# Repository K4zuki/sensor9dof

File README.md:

# sensor9dof
BMI160/BMM150 sensor board for MurataBLE board

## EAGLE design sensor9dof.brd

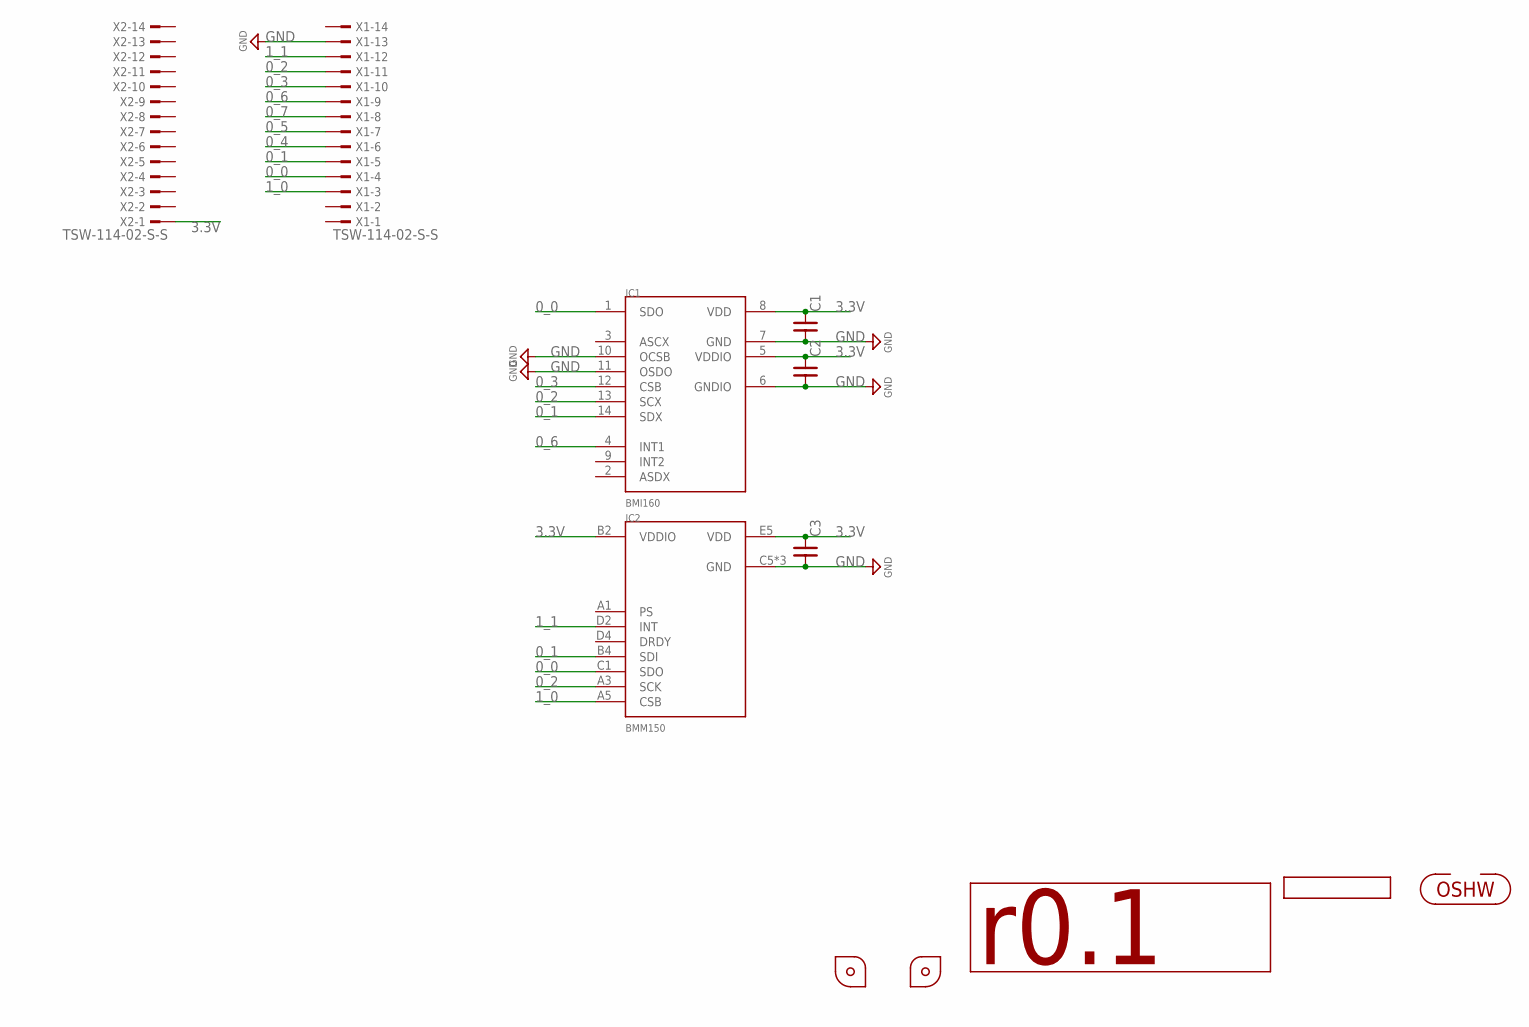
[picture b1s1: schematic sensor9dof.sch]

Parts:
C1, C2, C3: C_SMD_0.1U_1005; C0402
GIT1: GIT-REVISION_1.0; GIT-REVISION
IC1: BMI160
IC2: BMM150
ICON1: ICON_OSHW
ICON2: r0.1; ICON_REVISION2.0
P5: PCB_CORNER_NH
P6: PCB_CORNER
X1, X2: TSW-114-02-S-S; TSW-114-07-F-S

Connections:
0_0: IC1.1 (SDO), IC2.C1 (SDO), X1.4
0_1: IC1.14 (SDX), IC2.B4 (SDI), X1.5
0_2: IC1.13 (SCX), IC2.A3 (SCK), X1.11
0_3: IC1.12 (CSB), X1.10
0_4: X1.6
0_5: X1.7
0_6: IC1.4 (INT1), X1.9
0_7: X1.8
1_0: IC2.A5 (CSB), X1.3
1_1: IC2.D2 (INT), X1.12
3.3V: C1.1, C2.1, C3.1, IC1.5 (VDDIO), IC1.8 (VDD), IC2.B2 (VDDIO), IC2.E5 (VDD), X2.1
GND: C1.2, C2.2, C3.2, IC1.6 (GNDIO), IC1.7 (GND), IC1.10 (OCSB), IC1.11 (OSDO), IC2.C5 (GND), IC2.E1 (GND), IC2.E3 (GND), X1.13

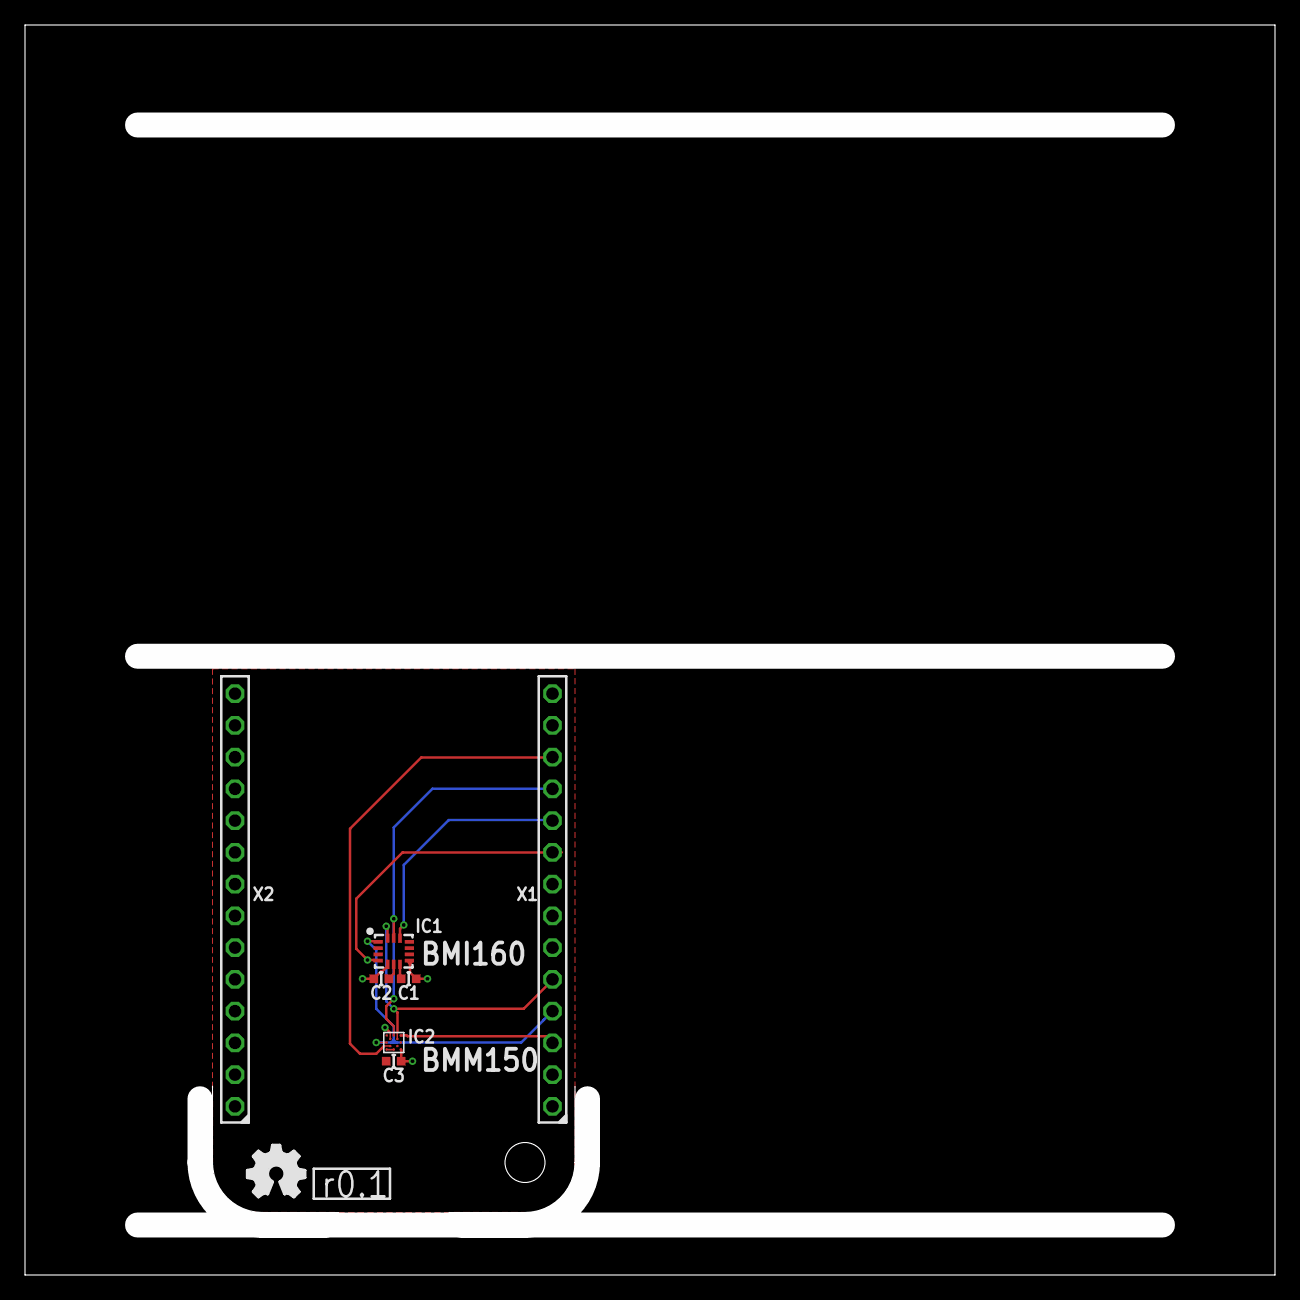
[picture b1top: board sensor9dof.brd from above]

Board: 2 copper layers, 100.0 x 100.0 mm, 12 parts (0 on the bottom side), 9 nets.

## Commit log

2017-07-26 initial commit
    - r0.1
2017-07-26 r0.1
2017-07-30 update tRestrict/bRestrict to 0.8mm width
